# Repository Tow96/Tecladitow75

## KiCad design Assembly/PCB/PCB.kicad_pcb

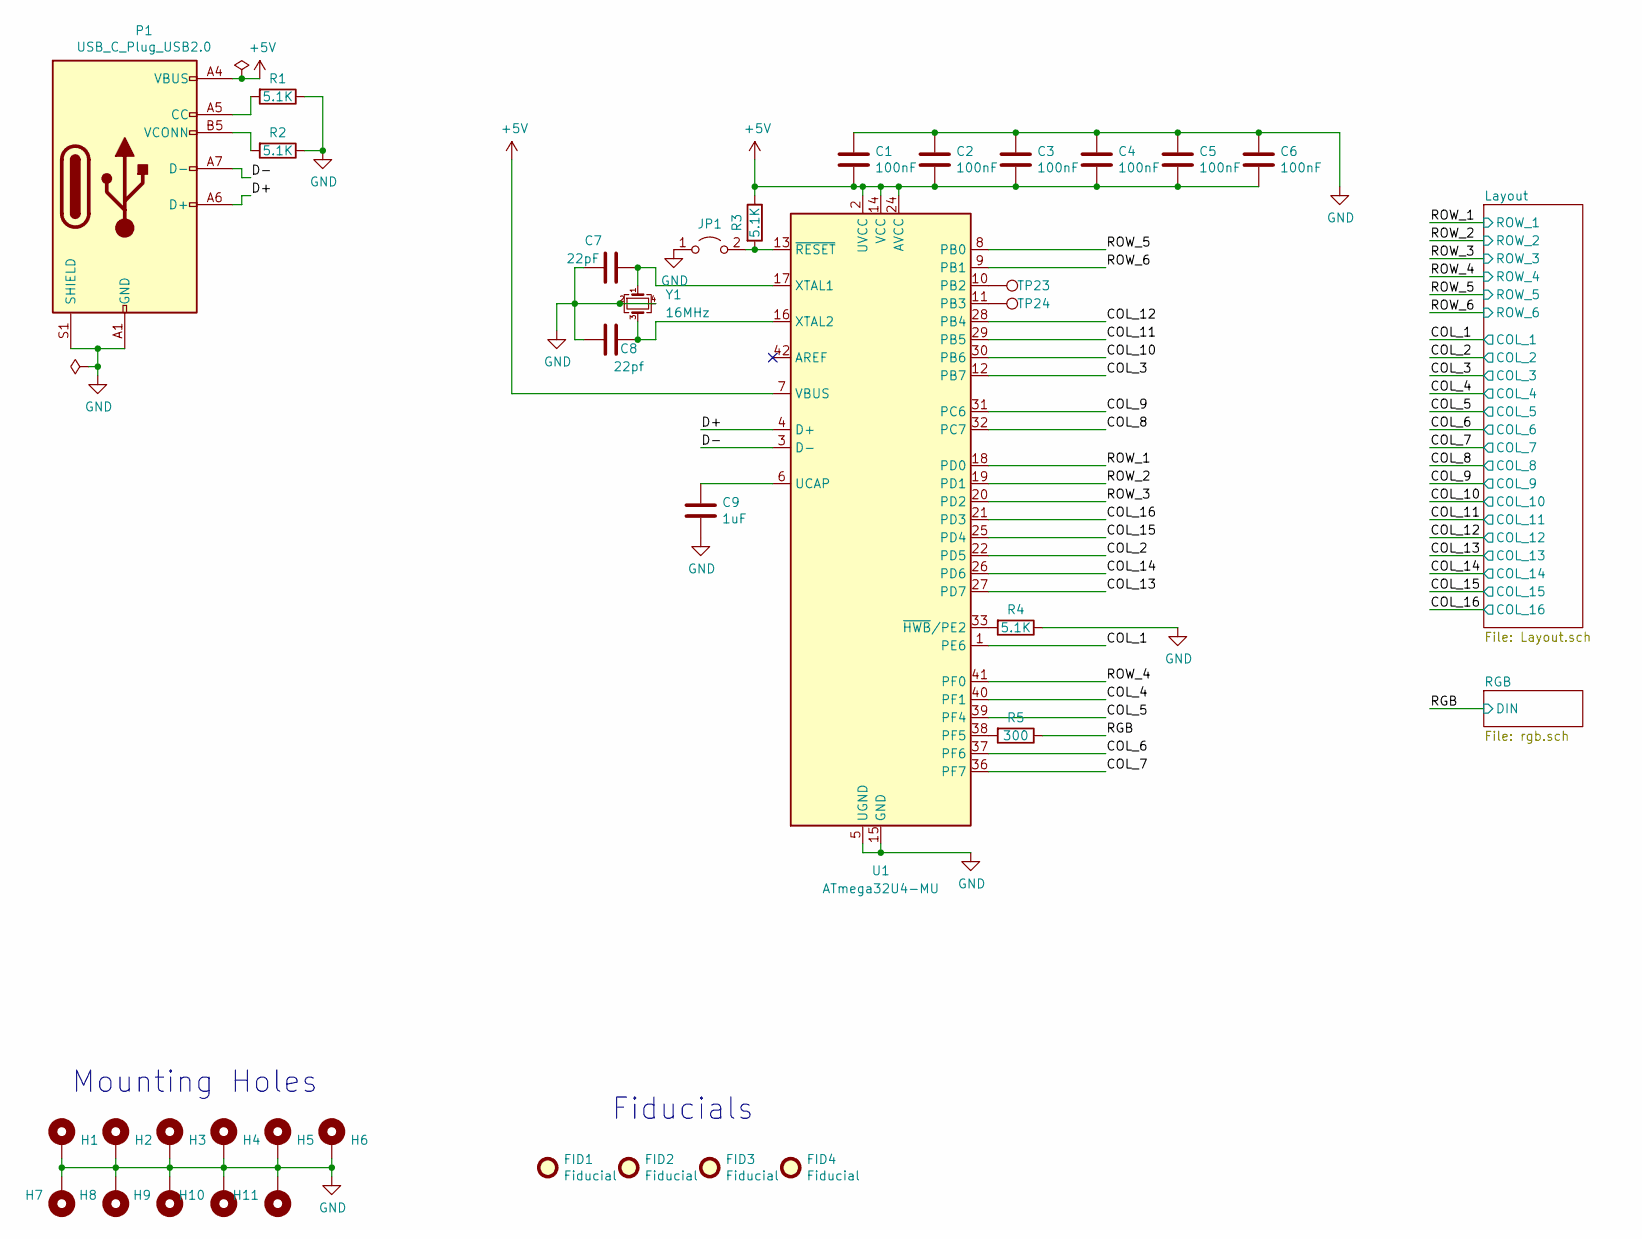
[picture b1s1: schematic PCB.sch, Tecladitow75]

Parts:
C1, C2, C3, C4, C5, C6: 100nF; C_0402_1005Metric; LCSC C106204
C7: 22pF; C_0402_1005Metric; LCSC C1555
C8: 22pf; C_0402_1005Metric; LCSC C1555
C9: 1uF; C_0402_1005Metric; LCSC C92755
FID1, FID2, FID3, FID4: Fiducial; Fiducial_0.75mm_Mask2.25mm
H1, H2, H3, H4, H5, H6, H7, H8, H9, H10, H11: MountingHole; MountingHole_2.7mm_M2.5_DIN965_Pad
JP1: Jumper_2_Open; PinSocket_1x02_P2.54mm_Vertical
P1: USB_C_Plug_USB2.0; FEMALE-USB-C_C2894898; LCSC C2894898
R1, R2, R3, R4: 5.1K; R_0402_1005Metric; LCSC C25905
R5: 300; R_0402_1005Metric; LCSC C25159
TP23, TP24: TestPoint; TestPoint_Pad_D1.5mm
U1: ATmega32U4-MU; QFN-44-1EP_7x7mm_P0.5mm_EP5.2x5.2mm
Y1: 16MHz; Crystal_SMD_3225-4Pin_3.2x2.5mm; LCSC C13738

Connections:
+5V: C1.2, C2.2, C3.2, C4.2, C5.2, C6.2, P1.A4 (VBUS), P1.A9 (VBUS), P1.B4 (VBUS), P1.B9 (VBUS), R3.1, U1.2 (UVCC), U1.7 (VBUS), U1.14 (VCC), U1.24 (AVCC), U1.34 (VCC), U1.44 (AVCC); also elsewhere on the board
/COL_1: U1.1 (PE6); also elsewhere on the board
/COL_2: U1.22 (PD5); also elsewhere on the board
/COL_3: U1.12 (PB7); also elsewhere on the board
/COL_4: U1.40 (PF1); also elsewhere on the board
/COL_5: U1.39 (PF4); also elsewhere on the board
/COL_6: U1.37 (PF6); also elsewhere on the board
/COL_7: U1.36 (PF7); also elsewhere on the board
/COL_8: U1.32 (PC7); also elsewhere on the board
/COL_9: U1.31 (PC6); also elsewhere on the board
/COL_10: U1.30 (PB6); also elsewhere on the board
/COL_11: U1.29 (PB5); also elsewhere on the board
/COL_12: U1.28 (PB4); also elsewhere on the board
/COL_13: U1.27 (PD7); also elsewhere on the board
/COL_14: U1.26 (PD6); also elsewhere on the board
/COL_15: U1.25 (PD4); also elsewhere on the board
/COL_16: U1.21 (PD3); also elsewhere on the board
/D+: P1.A6 (D+), U1.4 (D+)
/D-: P1.A7 (D-), U1.3 (D-)
/RGB: R5.1; also elsewhere on the board
/ROW_1: U1.18 (PD0); also elsewhere on the board
/ROW_2: U1.19 (PD1); also elsewhere on the board
/ROW_3: U1.20 (PD2); also elsewhere on the board
/ROW_4: U1.41 (PF0); also elsewhere on the board
/ROW_5: U1.8 (PB0); also elsewhere on the board
/ROW_6: U1.9 (PB1); also elsewhere on the board
GND: C1.1, C2.1, C3.1, C4.1, C5.1, C6.1, C7.2, C8.2, C9.2, H1.1, H2.1, H3.1, H4.1, H5.1, H6.1, H7.1, H8.1, H9.1, H10.1, H11.1, JP1.1 (A), P1.A1 (GND), P1.A12 (GND), P1.B1 (GND), P1.B12 (GND), P1.S1 (SHIELD), R1.1, R2.1, R4.1, U1.5 (UGND), U1.15 (GND), U1.23 (GND), U1.35 (GND), U1.43 (GND), U1.45 (GND), Y1.2, Y1.4; also elsewhere on the board
unnamed: C7.1, U1.17 (XTAL1), Y1.1
unnamed: C8.1, U1.16 (XTAL2), Y1.3
unnamed: C9.1, U1.6 (UCAP)
unnamed: JP1.2 (B), R3.2, U1.13 (~RESET)
unnamed: P1.A5 (CC), R1.2
unnamed: P1.B5 (VCONN), R2.2
unnamed: R4.2, U1.33 (~HWB~/PE2)
unnamed: R5.2, U1.38 (PF5)
unnamed: TP23.1, U1.10 (PB2)
unnamed: TP24.1, U1.11 (PB3)

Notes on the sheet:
Mounting Holes
Fiducials

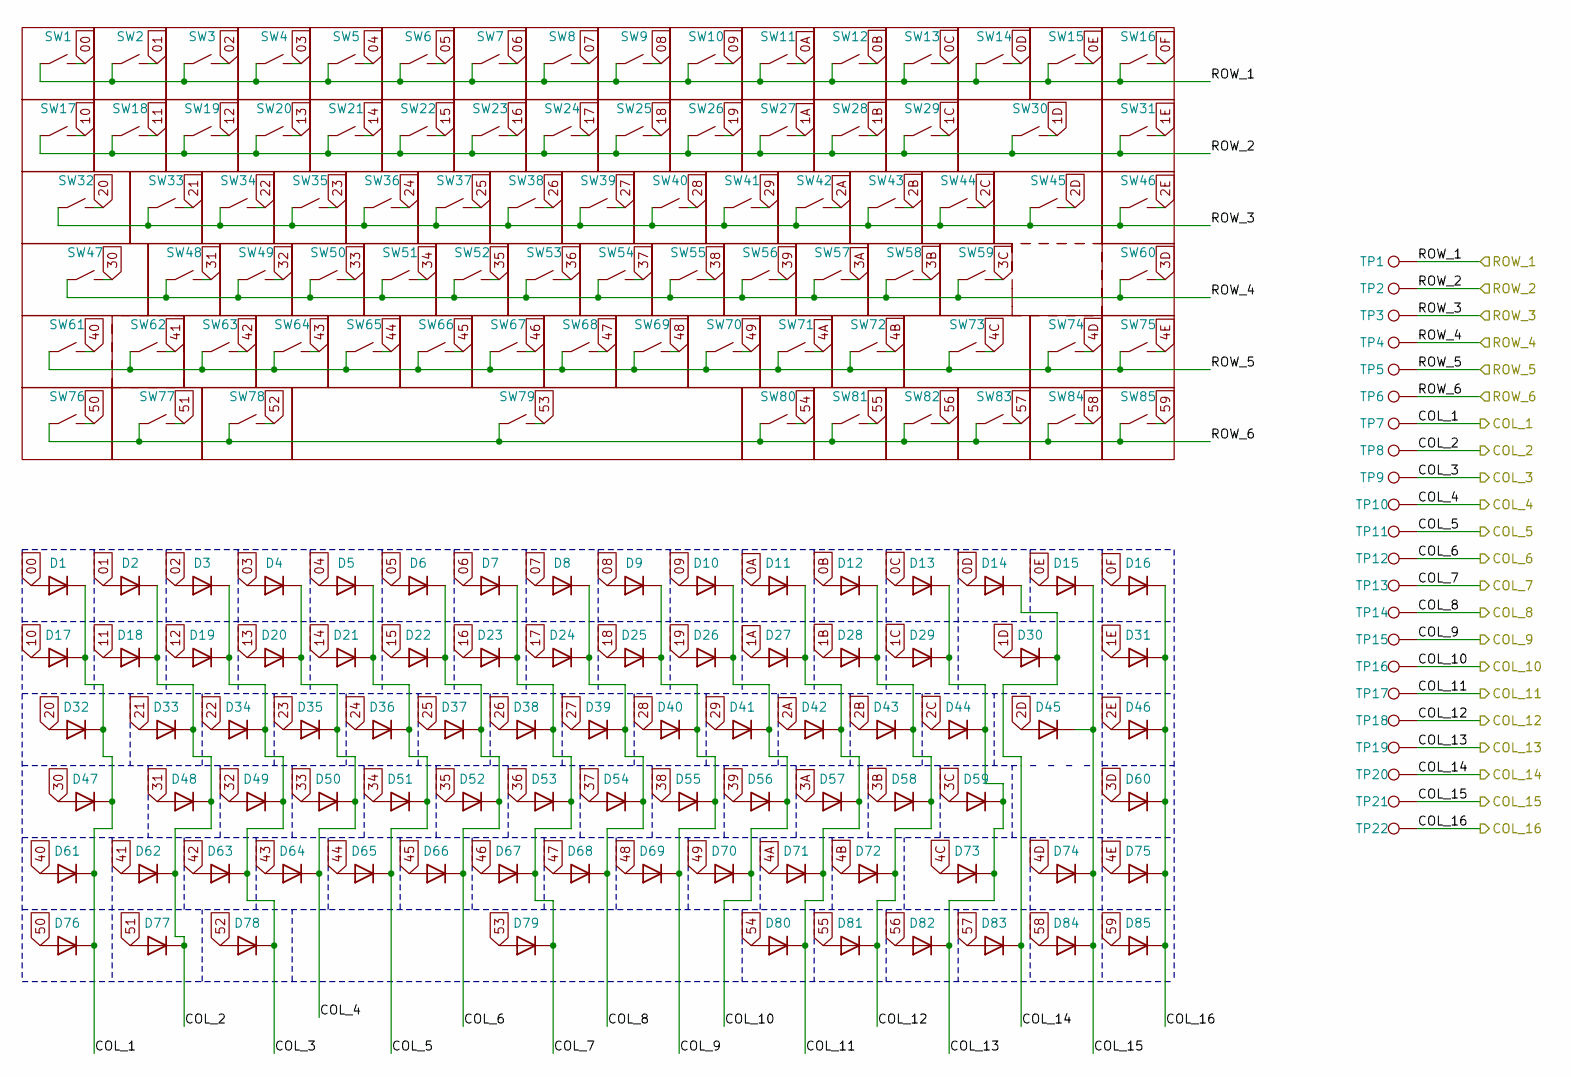
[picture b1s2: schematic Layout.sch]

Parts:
D1, D2, D3, D4, D5, D6, D7, D8, D9, D10, D11, D12, D13, D14, D15, D16, D17, D18, D19, D20, D21, D22, D23, D24, D25, D26, D27, D28, D29, D30, D31, D32, D33, D34, D35, D36, D37, D38, D39, D40, D41, D42, D43, D44, D45, D46, D47, D48, D49, D50, D51, D52, D53, D54, D55, D56, D57, D58, D59, D60, D61, D62, D63, D64, D65, D66, D67, D68, D69, D70, D71, D72, D73, D74, D75, D76, D77, D78, D79, D80, D81, D82, D83, D84, D85: D; D_SOD-323; LCSC C448648
SW1, SW2, SW3, SW4, SW5, SW6, SW7, SW8, SW9, SW10, SW11, SW12, SW13, SW14, SW15, SW16, SW17, SW18, SW19, SW20, SW21, SW22, SW23, SW24, SW25, SW26, SW27, SW28, SW29, SW31, SW33, SW34, SW35, SW36, SW37, SW38, SW39, SW40, SW41, SW42, SW43, SW44, SW46, SW48, SW49, SW50, SW51, SW52, SW53, SW54, SW55, SW56, SW57, SW58, SW60, SW62, SW63, SW64, SW65, SW66, SW67, SW68, SW69, SW70, SW71, SW72, SW74, SW75, SW80, SW81, SW82, SW83, SW84, SW85: SW_1U
SW30: SW_2U
SW32: SW_1.5U; SW_1U
SW45: SW_ENTER_ANSIISO; SW_Enter_ANSI-ISO
SW47: SW_1.75U; SW_CAPS+STAG
SW59: SW_PIPE_ANSIISO; SW_Pipe_ANSI-ISO
SW61: SW_LSHIFT_ANSIISO; SW_LSHIFT_ANSI-ISO
SW73: SW_1.75U; SW_1U
SW76, SW77, SW78: SW_1.25; SW_1U
SW79: SW_6.25U
TP1, TP2, TP3, TP4, TP5, TP6, TP7, TP8, TP9, TP10, TP11, TP12, TP13, TP14, TP15, TP16, TP17, TP18, TP19, TP20, TP21, TP22: TestPoint; TestPoint_Pad_D1.5mm

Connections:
00: D1.2 (A), SW1.2
0A: D11.2 (A), SW11.2
0B: D12.2 (A), SW12.2
0C: D13.2 (A), SW13.2
0D: D14.2 (A), SW14.2
0E: D15.2 (A), SW15.2
0F: D16.2 (A), SW16.2
01: D2.2 (A), SW2.2
1A: D27.2 (A), SW27.2
1B: D28.2 (A), SW28.2
1C: D29.2 (A), SW29.2
1D: D30.2 (A), SW30.2
1E: D31.2 (A), SW31.2
02: D3.2 (A), SW3.2
2A: D42.2 (A), SW42.2
2B: D43.2 (A), SW43.2
2C: D44.2 (A), SW44.2
2D: D45.2 (A), SW45.2
2E: D46.2 (A), SW46.2
03: D4.2 (A), SW4.2
3A: D57.2 (A), SW57.2
3B: D58.2 (A), SW58.2
3C: D59.2 (A), SW59.2
3D: D60.2 (A), SW60.2
04: D5.2 (A), SW5.2
4A: D71.2 (A), SW71.2
4B: D72.2 (A), SW72.2
4C: D73.2 (A), SW73.2
4D: D74.2 (A), SW74.2
4E: D75.2 (A), SW75.2
05: D6.2 (A), SW6.2
06: D7.2 (A), SW7.2
07: D8.2 (A), SW8.2
08: D9.2 (A), SW9.2
09: D10.2 (A), SW10.2
10: D17.2 (A), SW17.2
11: D18.2 (A), SW18.2
12: D19.2 (A), SW19.2
13: D20.2 (A), SW20.2
14: D21.2 (A), SW21.2
15: D22.2 (A), SW22.2
16: D23.2 (A), SW23.2
17: D24.2 (A), SW24.2
18: D25.2 (A), SW25.2
19: D26.2 (A), SW26.2
20: D32.2 (A), SW32.2
21: D33.2 (A), SW33.2
22: D34.2 (A), SW34.2
23: D35.2 (A), SW35.2
24: D36.2 (A), SW36.2
25: D37.2 (A), SW37.2
26: D38.2 (A), SW38.2
27: D39.2 (A), SW39.2
28: D40.2 (A), SW40.2
29: D41.2 (A), SW41.2
30: D47.2 (A), SW47.2
31: D48.2 (A), SW48.2
32: D49.2 (A), SW49.2
33: D50.2 (A), SW50.2
34: D51.2 (A), SW51.2
35: D52.2 (A), SW52.2
36: D53.2 (A), SW53.2
37: D54.2 (A), SW54.2
38: D55.2 (A), SW55.2
39: D56.2 (A), SW56.2
40: D61.2 (A), SW61.2
41: D62.2 (A), SW62.2
42: D63.2 (A), SW63.2
43: D64.2 (A), SW64.2
44: D65.2 (A), SW65.2
45: D66.2 (A), SW66.2
46: D67.2 (A), SW67.2
47: D68.2 (A), SW68.2
48: D69.2 (A), SW69.2
49: D70.2 (A), SW70.2
50: D76.2 (A), SW76.2
51: D77.2 (A), SW77.2
52: D78.2 (A), SW78.2
53: D79.2 (A), SW79.2
54: D80.2 (A), SW80.2
55: D81.2 (A), SW81.2
56: D82.2 (A), SW82.2
57: D83.2 (A), SW83.2
58: D84.2 (A), SW84.2
59: D85.2 (A), SW85.2
/COL_1: D1.1 (K), D17.1 (K), D32.1 (K), D47.1 (K), D61.1 (K), D76.1 (K), TP7.1; also elsewhere on the board
/COL_2: D2.1 (K), D18.1 (K), D33.1 (K), D48.1 (K), D62.1 (K), D77.1 (K), TP8.1; also elsewhere on the board
/COL_3: D3.1 (K), D19.1 (K), D34.1 (K), D49.1 (K), D63.1 (K), D78.1 (K), TP9.1; also elsewhere on the board
/COL_4: D4.1 (K), D20.1 (K), D35.1 (K), D50.1 (K), D64.1 (K), TP10.1; also elsewhere on the board
/COL_5: D5.1 (K), D21.1 (K), D36.1 (K), D51.1 (K), D65.1 (K), TP11.1; also elsewhere on the board
/COL_6: D6.1 (K), D22.1 (K), D37.1 (K), D52.1 (K), D66.1 (K), TP12.1; also elsewhere on the board
/COL_7: D7.1 (K), D23.1 (K), D38.1 (K), D53.1 (K), D67.1 (K), D79.1 (K), TP13.1; also elsewhere on the board
/COL_8: D8.1 (K), D24.1 (K), D39.1 (K), D54.1 (K), D68.1 (K), TP14.1; also elsewhere on the board
/COL_9: D9.1 (K), D25.1 (K), D40.1 (K), D55.1 (K), D69.1 (K), TP15.1; also elsewhere on the board
/COL_10: D10.1 (K), D26.1 (K), D41.1 (K), D56.1 (K), D70.1 (K), TP16.1; also elsewhere on the board
/COL_11: D11.1 (K), D27.1 (K), D42.1 (K), D57.1 (K), D71.1 (K), D80.1 (K), TP17.1; also elsewhere on the board
/COL_12: D12.1 (K), D28.1 (K), D43.1 (K), D58.1 (K), D72.1 (K), D81.1 (K), TP18.1; also elsewhere on the board
/COL_13: D13.1 (K), D29.1 (K), D44.1 (K), D59.1 (K), D73.1 (K), D82.1 (K), TP19.1; also elsewhere on the board
/COL_14: D14.1 (K), D30.1 (K), D83.1 (K), TP20.1; also elsewhere on the board
/COL_15: D15.1 (K), D45.1 (K), D74.1 (K), D84.1 (K), TP21.1; also elsewhere on the board
/COL_16: D16.1 (K), D31.1 (K), D46.1 (K), D60.1 (K), D75.1 (K), D85.1 (K), TP22.1; also elsewhere on the board
/ROW_1: SW1.1, SW2.1, SW3.1, SW4.1, SW5.1, SW6.1, SW7.1, SW8.1, SW9.1, SW10.1, SW11.1, SW12.1, SW13.1, SW14.1, SW15.1, SW16.1, TP1.1; also elsewhere on the board
/ROW_2: SW17.1, SW18.1, SW19.1, SW20.1, SW21.1, SW22.1, SW23.1, SW24.1, SW25.1, SW26.1, SW27.1, SW28.1, SW29.1, SW30.1, SW31.1, TP2.1; also elsewhere on the board
/ROW_3: SW32.1, SW33.1, SW34.1, SW35.1, SW36.1, SW37.1, SW38.1, SW39.1, SW40.1, SW41.1, SW42.1, SW43.1, SW44.1, SW45.1, SW46.1, TP3.1; also elsewhere on the board
/ROW_4: SW47.1, SW48.1, SW49.1, SW50.1, SW51.1, SW52.1, SW53.1, SW54.1, SW55.1, SW56.1, SW57.1, SW58.1, SW59.1, SW60.1, TP4.1; also elsewhere on the board
/ROW_5: SW61.1, SW62.1, SW63.1, SW64.1, SW65.1, SW66.1, SW67.1, SW68.1, SW69.1, SW70.1, SW71.1, SW72.1, SW73.1, SW74.1, SW75.1, TP5.1; also elsewhere on the board
/ROW_6: SW76.1, SW77.1, SW78.1, SW79.1, SW80.1, SW81.1, SW82.1, SW83.1, SW84.1, SW85.1, TP6.1; also elsewhere on the board

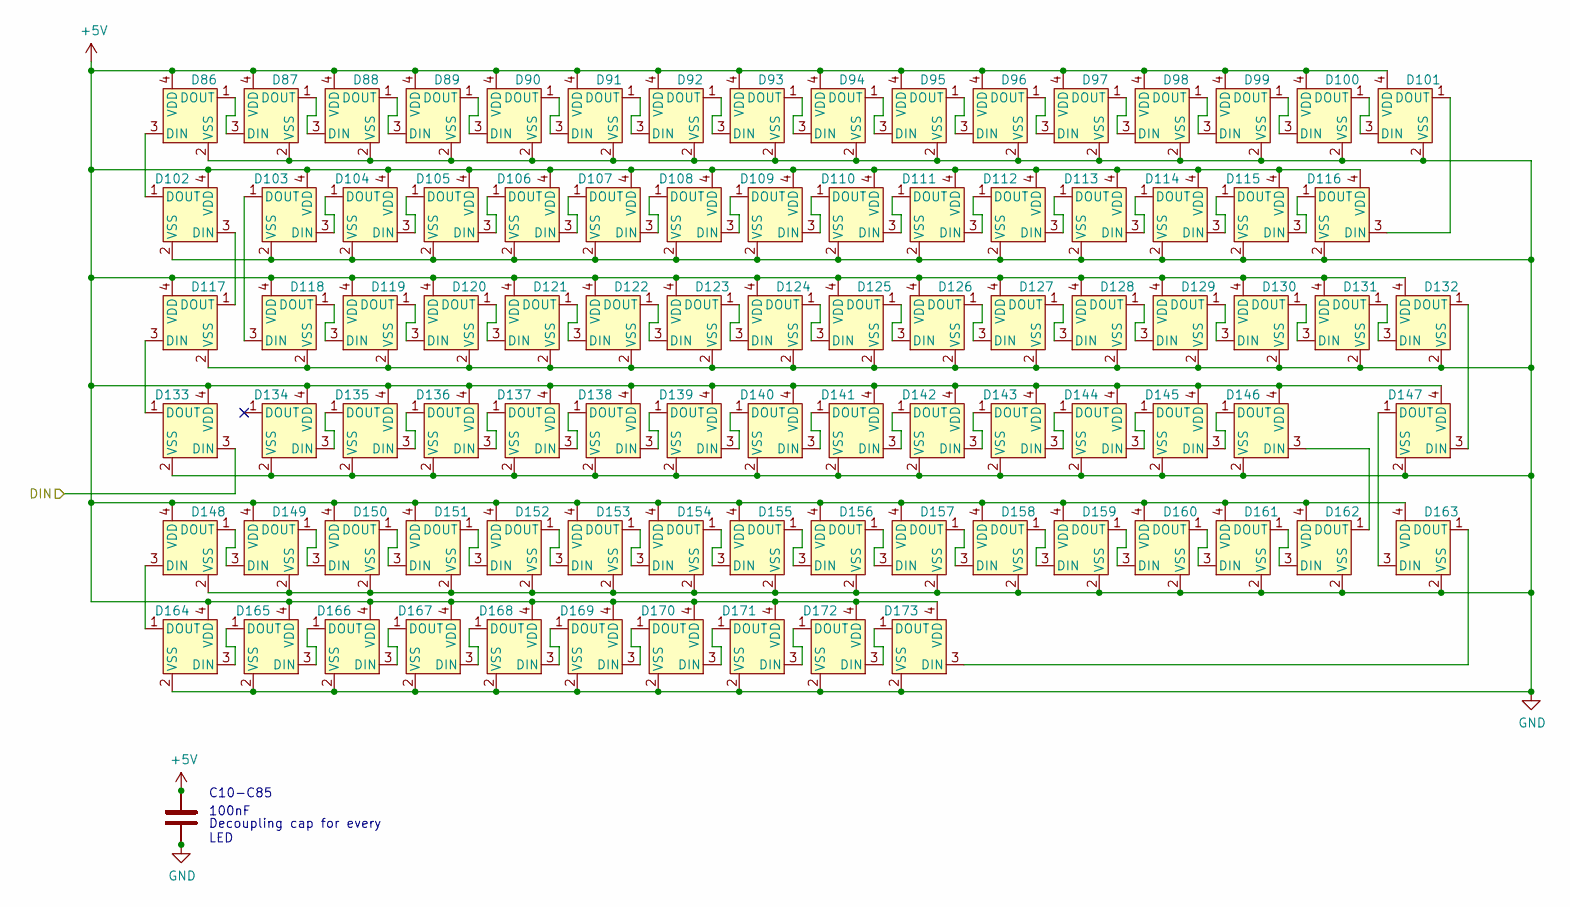
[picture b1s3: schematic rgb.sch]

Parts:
C10, C11, C12, C13, C14, C15, C16, C17, C18, C19, C20, C21, C22, C23, C24, C25, C26, C27, C28, C29, C30, C31, C32, C33, C34, C35, C36, C37, C38, C39, C40, C41, C42, C43, C44, C45, C46, C47, C48, C49, C50, C51, C52, C53, C54, C55, C56, C57, C58, C59, C60, C61, C62, C63, C64, C65, C66, C67, C68, C69, C70, C71, C72, C73, C74, C75, C76, C77, C78, C79, C80, C81, C82, C83, C84, C85, C86, C87, C88, C89, C90, C91, C92, C93, C94, C95, C96, C97: 100nF; C_0402_1005Metric; LCSC C106204
D86, D87, D88, D89, D90, D91, D92, D93, D94, D95, D96, D97, D98, D99, D100, D101, D102, D103, D104, D105, D106, D107, D108, D109, D110, D111, D112, D113, D114, D115, D116, D117, D118, D119, D120, D121, D122, D123, D124, D125, D126, D127, D128, D129, D130, D131, D132, D133, D134, D135, D136, D137, D138, D139, D140, D141, D142, D143, D144, D145, D146, D147, D148, D149, D150, D151, D152, D153, D154, D155, D156, D157, D158, D159, D160, D161, D162, D163, D164, D165, D166, D167, D168, D169, D170, D171, D172, D173: SK6812MINI-compact; SK6812Mini-e_passtrough

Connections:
+5V: C10.1, C11.1, C12.1, C13.1, C14.1, C15.1, C16.1, C17.1, C18.1, C19.1, C20.1, C21.1, C22.1, C23.1, C24.1, C25.1, C26.1, C27.1, C28.1, C29.1, C30.1, C31.1, C32.1, C33.1, C34.1, C35.1, C36.1, C37.1, C38.1, C39.1, C40.1, C41.1, C42.1, C43.1, C44.1, C45.1, C46.1, C47.1, C48.1, C49.1, C50.1, C51.1, C52.1, C53.1, C54.1, C55.1, C56.1, C57.1, C58.1, C59.1, C60.1, C61.1, C62.1, C63.1, C64.1, C65.1, C66.1, C67.1, C68.1, C69.1, C70.1, C71.1, C72.1, C73.1, C74.1, C75.1, C76.1, C77.1, C78.1, C79.1, C80.1, C81.1, C82.1, C83.1, C84.1, C85.1, C86.1, C87.1, C88.1, C89.1, C90.1, C91.1, C92.1, C93.1, C94.1, C95.1, C96.1, C97.1, D86.4 (VDD), D87.4 (VDD), D88.4 (VDD), D89.4 (VDD), D90.4 (VDD), D91.4 (VDD), D92.4 (VDD), D93.4 (VDD), D94.4 (VDD), D95.4 (VDD), D96.4 (VDD), D97.4 (VDD), D98.4 (VDD), D99.4 (VDD), D100.4 (VDD), D101.4 (VDD), D102.4 (VDD), D103.4 (VDD), D104.4 (VDD), D105.4 (VDD), D106.4 (VDD), D107.4 (VDD), D108.4 (VDD), D109.4 (VDD), D110.4 (VDD), D111.4 (VDD), D112.4 (VDD), D113.4 (VDD), D114.4 (VDD), D115.4 (VDD), D116.4 (VDD), D117.4 (VDD), D118.4 (VDD), D119.4 (VDD), D120.4 (VDD), D121.4 (VDD), D122.4 (VDD), D123.4 (VDD), D124.4 (VDD), D125.4 (VDD), D126.4 (VDD), D127.4 (VDD), D128.4 (VDD), D129.4 (VDD), D130.4 (VDD), D131.4 (VDD), D132.4 (VDD), D133.4 (VDD), D134.4 (VDD), D135.4 (VDD), D136.4 (VDD), D137.4 (VDD), D138.4 (VDD), D139.4 (VDD), D140.4 (VDD), D141.4 (VDD), D142.4 (VDD), D143.4 (VDD), D144.4 (VDD), D145.4 (VDD), D146.4 (VDD), D147.4 (VDD), D148.4 (VDD), D149.4 (VDD), D150.4 (VDD), D151.4 (VDD), D152.4 (VDD), D153.4 (VDD), D154.4 (VDD), D155.4 (VDD), D156.4 (VDD), D157.4 (VDD), D158.4 (VDD), D159.4 (VDD), D160.4 (VDD), D161.4 (VDD), D162.4 (VDD), D163.4 (VDD), D164.4 (VDD), D165.4 (VDD), D166.4 (VDD), D167.4 (VDD), D168.4 (VDD), D169.4 (VDD), D170.4 (VDD), D171.4 (VDD), D172.4 (VDD), D173.4 (VDD); also elsewhere on the board
/RGB: D133.3 (DIN); also elsewhere on the board
GND: C10.2, C11.2, C12.2, C13.2, C14.2, C15.2, C16.2, C17.2, C18.2, C19.2, C20.2, C21.2, C22.2, C23.2, C24.2, C25.2, C26.2, C27.2, C28.2, C29.2, C30.2, C31.2, C32.2, C33.2, C34.2, C35.2, C36.2, C37.2, C38.2, C39.2, C40.2, C41.2, C42.2, C43.2, C44.2, C45.2, C46.2, C47.2, C48.2, C49.2, C50.2, C51.2, C52.2, C53.2, C54.2, C55.2, C56.2, C57.2, C58.2, C59.2, C60.2, C61.2, C62.2, C63.2, C64.2, C65.2, C66.2, C67.2, C68.2, C69.2, C70.2, C71.2, C72.2, C73.2, C74.2, C75.2, C76.2, C77.2, C78.2, C79.2, C80.2, C81.2, C82.2, C83.2, C84.2, C85.2, C86.2, C87.2, C88.2, C89.2, C90.2, C91.2, C92.2, C93.2, C94.2, C95.2, C96.2, C97.2, D86.2 (VSS), D87.2 (VSS), D88.2 (VSS), D89.2 (VSS), D90.2 (VSS), D91.2 (VSS), D92.2 (VSS), D93.2 (VSS), D94.2 (VSS), D95.2 (VSS), D96.2 (VSS), D97.2 (VSS), D98.2 (VSS), D99.2 (VSS), D100.2 (VSS), D101.2 (VSS), D102.2 (VSS), D103.2 (VSS), D104.2 (VSS), D105.2 (VSS), D106.2 (VSS), D107.2 (VSS), D108.2 (VSS), D109.2 (VSS), D110.2 (VSS), D111.2 (VSS), D112.2 (VSS), D113.2 (VSS), D114.2 (VSS), D115.2 (VSS), D116.2 (VSS), D117.2 (VSS), D118.2 (VSS), D119.2 (VSS), D120.2 (VSS), D121.2 (VSS), D122.2 (VSS), D123.2 (VSS), D124.2 (VSS), D125.2 (VSS), D126.2 (VSS), D127.2 (VSS), D128.2 (VSS), D129.2 (VSS), D130.2 (VSS), D131.2 (VSS), D132.2 (VSS), D133.2 (VSS), D134.2 (VSS), D135.2 (VSS), D136.2 (VSS), D137.2 (VSS), D138.2 (VSS), D139.2 (VSS), D140.2 (VSS), D141.2 (VSS), D142.2 (VSS), D143.2 (VSS), D144.2 (VSS), D145.2 (VSS), D146.2 (VSS), D147.2 (VSS), D148.2 (VSS), D149.2 (VSS), D150.2 (VSS), D151.2 (VSS), D152.2 (VSS), D153.2 (VSS), D154.2 (VSS), D155.2 (VSS), D156.2 (VSS), D157.2 (VSS), D158.2 (VSS), D159.2 (VSS), D160.2 (VSS), D161.2 (VSS), D162.2 (VSS), D163.2 (VSS), D164.2 (VSS), D165.2 (VSS), D166.2 (VSS), D167.2 (VSS), D168.2 (VSS), D169.2 (VSS), D170.2 (VSS), D171.2 (VSS), D172.2 (VSS), D173.2 (VSS); also elsewhere on the board
unnamed: D86.1 (DOUT), D87.3 (DIN)
unnamed: D87.1 (DOUT), D88.3 (DIN)
unnamed: D88.1 (DOUT), D89.3 (DIN)
unnamed: D89.1 (DOUT), D90.3 (DIN)
unnamed: D90.1 (DOUT), D91.3 (DIN)
unnamed: D91.1 (DOUT), D92.3 (DIN)
unnamed: D92.1 (DOUT), D93.3 (DIN)
unnamed: D93.1 (DOUT), D94.3 (DIN)
unnamed: D94.1 (DOUT), D95.3 (DIN)
unnamed: D95.1 (DOUT), D96.3 (DIN)
unnamed: D96.1 (DOUT), D97.3 (DIN)
unnamed: D97.1 (DOUT), D98.3 (DIN)
unnamed: D98.1 (DOUT), D99.3 (DIN)
unnamed: D100.1 (DOUT), D101.3 (DIN)
unnamed: D99.1 (DOUT), D100.3 (DIN)
unnamed: D101.1 (DOUT), D116.3 (DIN)
unnamed: D86.3 (DIN), D102.1 (DOUT)
unnamed: D102.3 (DIN), D117.1 (DOUT)
unnamed: D103.1 (DOUT), D118.3 (DIN)
unnamed: D103.3 (DIN), D104.1 (DOUT)
unnamed: D104.3 (DIN), D105.1 (DOUT)
unnamed: D105.3 (DIN), D106.1 (DOUT)
unnamed: D106.3 (DIN), D107.1 (DOUT)
unnamed: D107.3 (DIN), D108.1 (DOUT)
unnamed: D108.3 (DIN), D109.1 (DOUT)
unnamed: D109.3 (DIN), D110.1 (DOUT)
unnamed: D110.3 (DIN), D111.1 (DOUT)
unnamed: D111.3 (DIN), D112.1 (DOUT)
unnamed: D112.3 (DIN), D113.1 (DOUT)
unnamed: D113.3 (DIN), D114.1 (DOUT)
unnamed: D114.3 (DIN), D115.1 (DOUT)
unnamed: D115.3 (DIN), D116.1 (DOUT)
unnamed: D117.3 (DIN), D133.1 (DOUT)
unnamed: D118.1 (DOUT), D119.3 (DIN)
unnamed: D119.1 (DOUT), D120.3 (DIN)
unnamed: D120.1 (DOUT), D121.3 (DIN)
unnamed: D121.1 (DOUT), D122.3 (DIN)
unnamed: D122.1 (DOUT), D123.3 (DIN)
unnamed: D123.1 (DOUT), D124.3 (DIN)
unnamed: D124.1 (DOUT), D125.3 (DIN)
unnamed: D125.1 (DOUT), D126.3 (DIN)
unnamed: D126.1 (DOUT), D127.3 (DIN)
unnamed: D127.1 (DOUT), D128.3 (DIN)
unnamed: D128.1 (DOUT), D129.3 (DIN)
unnamed: D129.1 (DOUT), D130.3 (DIN)
unnamed: D130.1 (DOUT), D131.3 (DIN)
unnamed: D131.1 (DOUT), D132.3 (DIN)
unnamed: D132.1 (DOUT), D147.3 (DIN)
unnamed: D134.3 (DIN), D135.1 (DOUT)
unnamed: D135.3 (DIN), D136.1 (DOUT)
unnamed: D136.3 (DIN), D137.1 (DOUT)
unnamed: D137.3 (DIN), D138.1 (DOUT)
unnamed: D138.3 (DIN), D139.1 (DOUT)
unnamed: D139.3 (DIN), D140.1 (DOUT)
unnamed: D140.3 (DIN), D141.1 (DOUT)
unnamed: D141.3 (DIN), D142.1 (DOUT)
unnamed: D142.3 (DIN), D143.1 (DOUT)
unnamed: D143.3 (DIN), D144.1 (DOUT)
unnamed: D144.3 (DIN), D145.1 (DOUT)
unnamed: D145.3 (DIN), D146.1 (DOUT)
unnamed: D146.3 (DIN), D162.1 (DOUT)
unnamed: D147.1 (DOUT), D163.3 (DIN)
unnamed: D148.1 (DOUT), D149.3 (DIN)
unnamed: D148.3 (DIN), D164.1 (DOUT)
unnamed: D149.1 (DOUT), D150.3 (DIN)
unnamed: D150.1 (DOUT), D151.3 (DIN)
unnamed: D151.1 (DOUT), D152.3 (DIN)
unnamed: D152.1 (DOUT), D153.3 (DIN)
unnamed: D153.1 (DOUT), D154.3 (DIN)
unnamed: D154.1 (DOUT), D155.3 (DIN)
unnamed: D155.1 (DOUT), D156.3 (DIN)
unnamed: D156.1 (DOUT), D157.3 (DIN)
unnamed: D157.1 (DOUT), D158.3 (DIN)
unnamed: D158.1 (DOUT), D159.3 (DIN)
unnamed: D159.1 (DOUT), D160.3 (DIN)
unnamed: D160.1 (DOUT), D161.3 (DIN)
unnamed: D161.1 (DOUT), D162.3 (DIN)
unnamed: D163.1 (DOUT), D173.3 (DIN)
unnamed: D164.3 (DIN), D165.1 (DOUT)
unnamed: D165.3 (DIN), D166.1 (DOUT)
unnamed: D166.3 (DIN), D167.1 (DOUT)
unnamed: D167.3 (DIN), D168.1 (DOUT)
unnamed: D168.3 (DIN), D169.1 (DOUT)
unnamed: D169.3 (DIN), D170.1 (DOUT)
unnamed: D170.3 (DIN), D171.1 (DOUT)
unnamed: D171.3 (DIN), D172.1 (DOUT)
unnamed: D172.3 (DIN), D173.1 (DOUT)

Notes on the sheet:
C10-C85
100nF
Decoupling cap for every LED

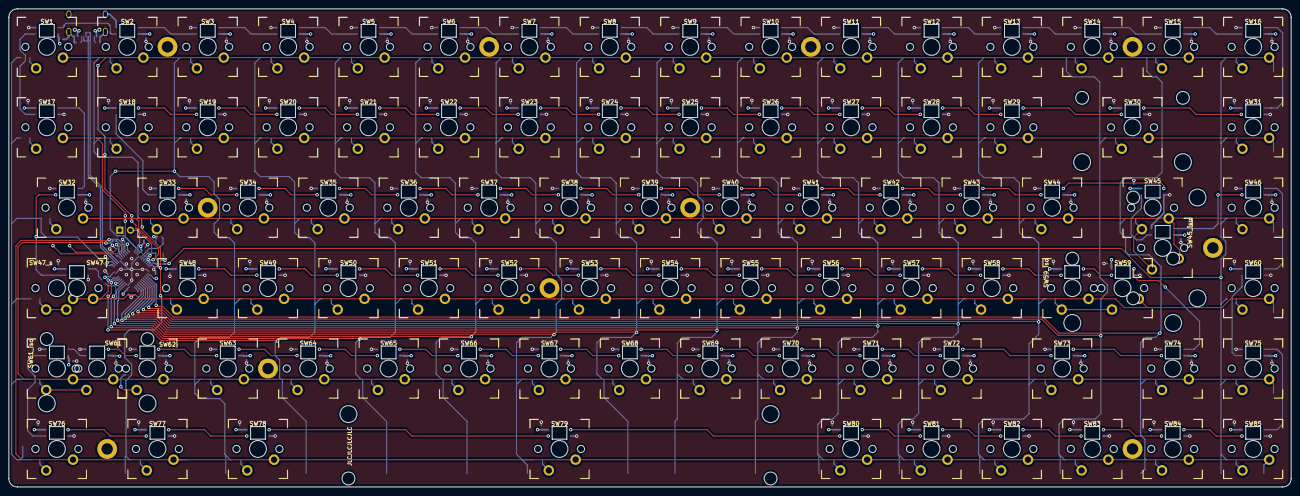
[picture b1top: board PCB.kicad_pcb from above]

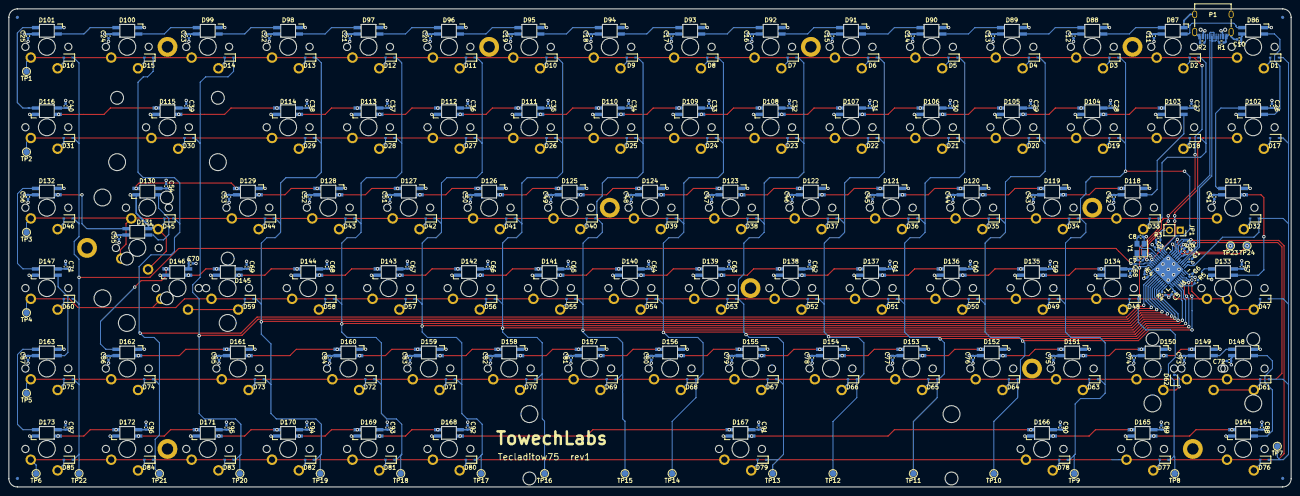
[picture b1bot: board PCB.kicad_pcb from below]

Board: 4 copper layers, 303.7 x 113.3 mm, 403 parts (307 on the bottom side), 209 nets.

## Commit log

2022-01-07 Adde various files
2022-01-07 Added descriptors for BOM generation
2022-01-09 Added Component_BOM
